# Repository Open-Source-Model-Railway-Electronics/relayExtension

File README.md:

# Relay Extension

These are general-purpose relay modules for use with DCC decoders like the [OS-Solenoid-Decoder](https://github.com/Open-Source-Model-Railway-Electronics/OS-Solenoid-Decoder).

## Variants

### SMD Version

### THT Version

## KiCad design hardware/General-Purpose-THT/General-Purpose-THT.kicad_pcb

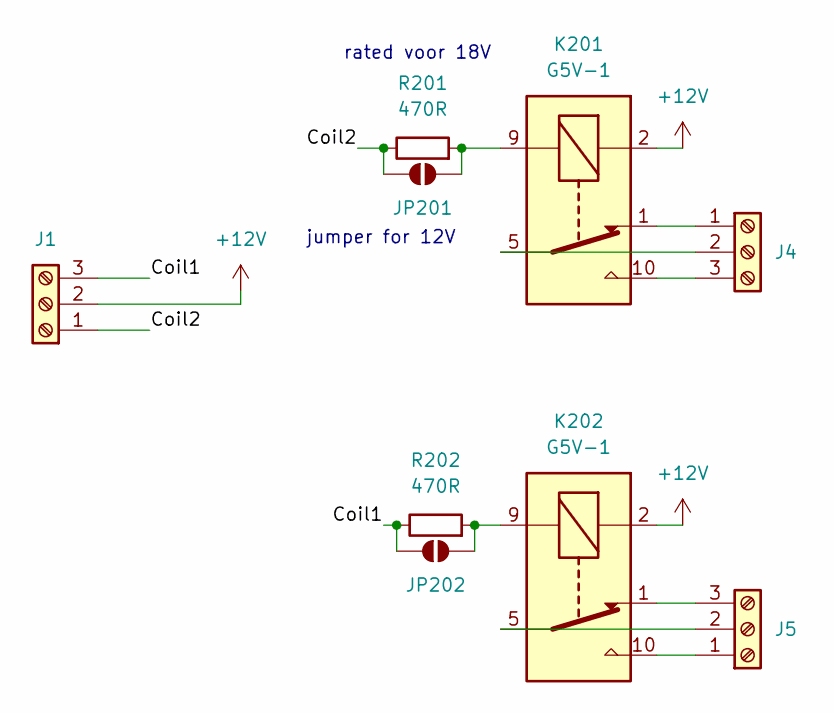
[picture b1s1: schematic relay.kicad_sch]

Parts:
J1: Screw_Terminal_01x03; connector_3.50mm_3P horizontal_MALE; JLCPCB Part# C6394074
J4: Screw_Terminal_01x03; PhoenixContact_MC_1,5_3-G-3.5_1x03_P3.50mm_Horizontal; JLCPCB Part# C22380440
J5: Screw_Terminal_01x03; PhoenixContact_MCV_1,5_3-G-3.5_1x03_P3.50mm_Vertical; Mating Part# C560231; JLCPCB Part# C192778
JP201, JP202: SolderJumper_2_Open; SolderJumper-2_P1.3mm_Open_RoundedPad1.0x1.5mm
K201, K202: G5V-1; Relay_SPDT_Omron_G5V-1
R201, R202: 470R; R_Axial_DIN0204_L3.6mm_D1.6mm_P7.62mm_Horizontal

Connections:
+12V: J1.2, K201.2, K202.2
/relay1/Coil1: J1.3, JP202.1 (A), R202.1
/relay1/Coil2: J1.1, JP201.1 (A), R201.1
unnamed: J4.1, K201.1
unnamed: J4.2, K201.5, K201.6
unnamed: J4.3, K201.10
unnamed: J5.1, K202.10
unnamed: J5.2, K202.5, K202.6
unnamed: J5.3, K202.1
unnamed: JP201.2 (B), K201.9, R201.2
unnamed: JP202.2 (B), K202.9, R202.2

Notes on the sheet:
jumper for 12V
rated voor 18V

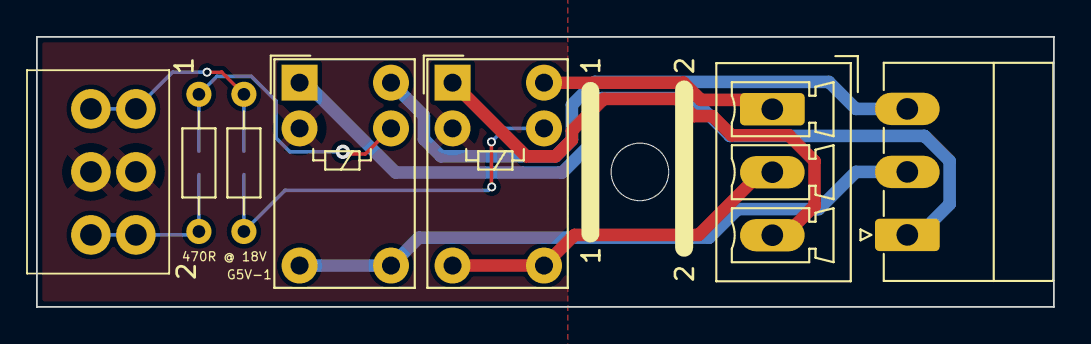
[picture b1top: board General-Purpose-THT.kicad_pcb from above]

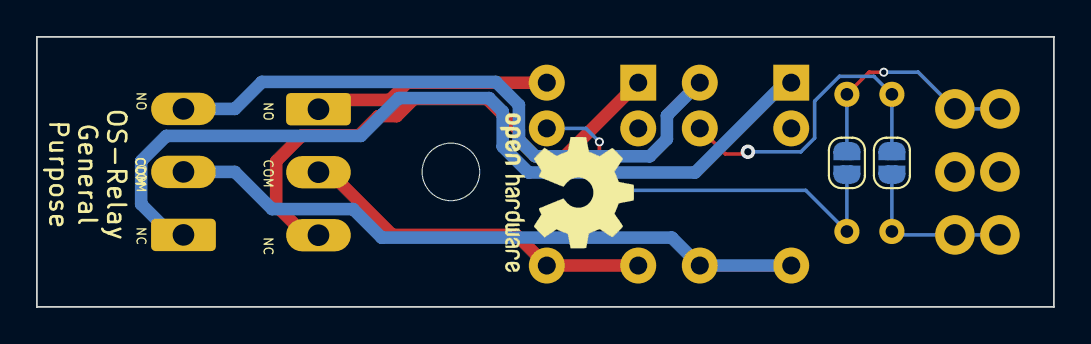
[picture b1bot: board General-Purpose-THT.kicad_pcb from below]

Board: 2 copper layers, 56.5 x 15.0 mm, 9 parts (2 on the bottom side), 11 nets.

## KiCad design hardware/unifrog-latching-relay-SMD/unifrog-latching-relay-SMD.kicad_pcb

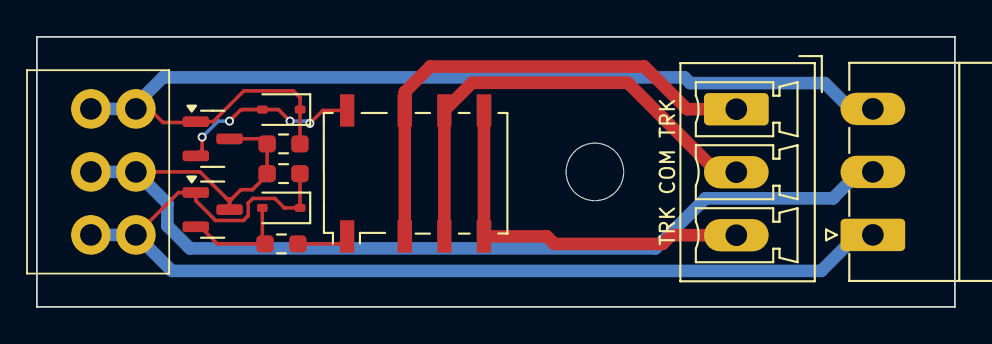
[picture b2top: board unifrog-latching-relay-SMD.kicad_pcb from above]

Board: 2 copper layers, 51.0 x 15.0 mm, 11 parts (0 on the bottom side), 9 nets.

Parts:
D3, D4: 1N4148WS; D_SOD-323
J1: Screw_Terminal_01x03; connector_3.50mm_3P horizontal_MALE
J4: Screw_Terminal_01x03; PhoenixContact_MC_1,5_3-G-3.5_1x03_P3.50mm_Horizontal
J6: Screw_Terminal_01x03; PhoenixContact_MCV_1,5_3-G-3.5_1x03_P3.50mm_Vertical
K2: G6KU-2; Relay_DPDT_Omron_G6K-2F-Y
Q3, Q4: NPN_TOR; SOT-23
R3, R4: 22k; R_0603_smalltext
R10: 680R; R_0603_smalltext

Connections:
/relay2/DCC_A: J6.1, K2.2, K2.7
/relay2/DCC_B: J6.3, K2.4, K2.5
/relay2/coilA: D4.1 (K), J1.1, J4.1, Q4.1 (B), R4.2
/relay2/coilB: D3.1 (K), J1.3, J4.3, Q3.1 (B), R3.2
/relay2/common: J1.2, J4.2, Q3.3 (C), Q4.3 (C), R3.1, R4.1
unnamed: D3.2 (A), K2.8, Q3.2 (E)
unnamed: D4.2 (A), Q4.2 (E), R10.1
unnamed: J6.2, K2.3, K2.6
unnamed: K2.1, R10.2

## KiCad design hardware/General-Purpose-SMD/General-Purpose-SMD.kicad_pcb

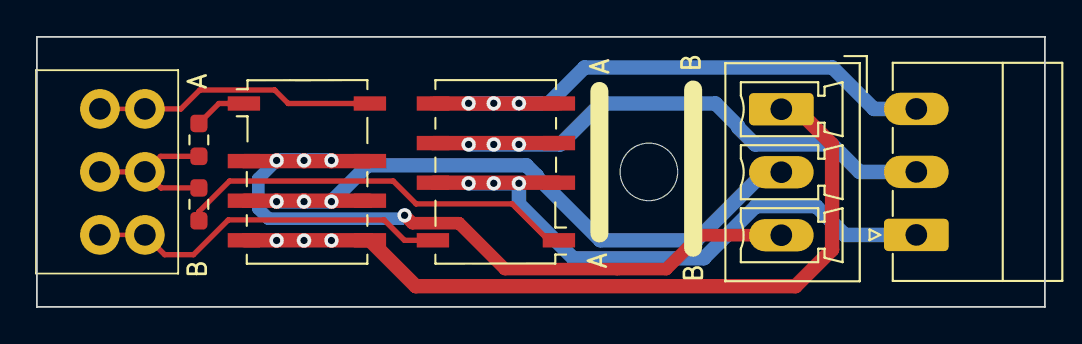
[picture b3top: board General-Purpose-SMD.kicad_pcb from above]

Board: 2 copper layers, 56.0 x 15.0 mm, 7 parts (0 on the bottom side), 11 nets.

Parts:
J1: Screw_Terminal_01x03; connector_3.50mm_3P horizontal_MALE
J4: Screw_Terminal_01x03; PhoenixContact_MC_1,5_3-G-3.5_1x03_P3.50mm_Horizontal
J5: Screw_Terminal_01x03; PhoenixContact_MCV_1,5_3-G-3.5_1x03_P3.50mm_Vertical
K1, K2: G6K-2F-Y-TR DC12; Relay_DPDT_Omron_G6K-2F-Y
R1, R2: 680R; R_0603_smalltext

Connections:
/relay1/COM1: J4.2, K1.3, K1.6
/relay1/COM2: J5.2, K2.3, K2.6
/relay1/Coil1: J1.3, K2.8
/relay1/Coil2: J1.1, K1.8
/relay1/NC1: J4.1, K1.2, K1.7
/relay1/NC2: J5.3, K2.2, K2.7
/relay1/NO1: J4.3, K1.4, K1.5
/relay1/NO2: J5.1, K2.4, K2.5
/relay1/V+: J1.2, R1.2, R2.2
unnamed: K1.1, R1.1
unnamed: K2.1, R2.1

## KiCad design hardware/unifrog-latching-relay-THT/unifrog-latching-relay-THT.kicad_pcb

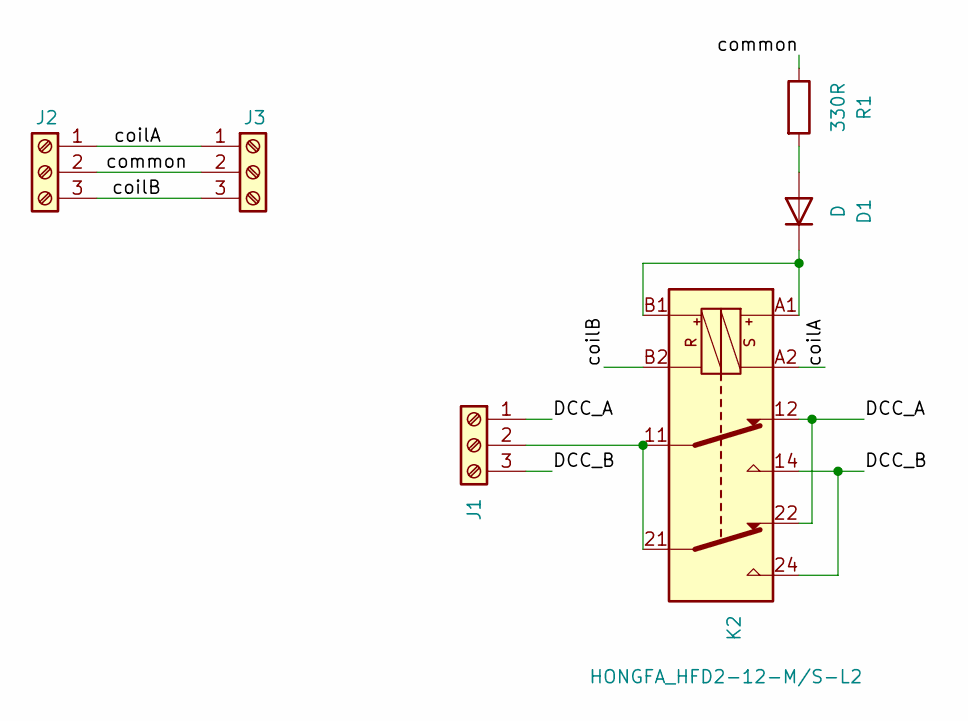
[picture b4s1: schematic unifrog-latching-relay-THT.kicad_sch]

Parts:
D1: D; D_DO-34_SOD68_P7.62mm_Horizontal
J1: Screw_Terminal_01x03; PhoenixContact_MCV_1,5_3-G-3.5_1x03_P3.50mm_Vertical; mating part# C560231; JLCPCB Part# C880555
J2: Screw_Terminal_01x03; connector_3.50mm_3P horizontal_MALE; JLCPCB Part# C6394074
J3: Screw_Terminal_01x03; PhoenixContact_MC_1,5_3-G-3.5_1x03_P3.50mm_Horizontal; Mating Part# C560213; JLCPCB Part# C880573
K2: HONGFA_HFD2-12-M/S-L2; Relay_DPDT_Omron_G6AK
R1: 330R; R_Axial_DIN0204_L3.6mm_D1.6mm_P7.62mm_Horizontal

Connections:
/DCC_A: J1.1, K2.12, K2.22
/DCC_B: J1.3, K2.14, K2.24
/coilA: J2.1, J3.1, K2.A2
/coilB: J2.3, J3.3, K2.B2
/common: J2.2, J3.2, R1.1
unnamed: D1.2 (A), R1.2
unnamed: D1.1 (K), K2.A1, K2.B1
unnamed: J1.2, K2.11, K2.21

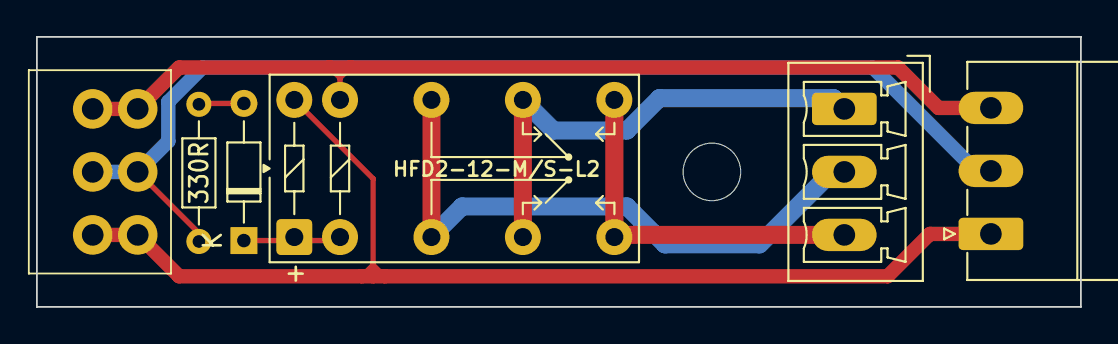
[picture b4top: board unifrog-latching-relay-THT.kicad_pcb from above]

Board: 2 copper layers, 58.0 x 15.0 mm, 6 parts (0 on the bottom side), 8 nets.

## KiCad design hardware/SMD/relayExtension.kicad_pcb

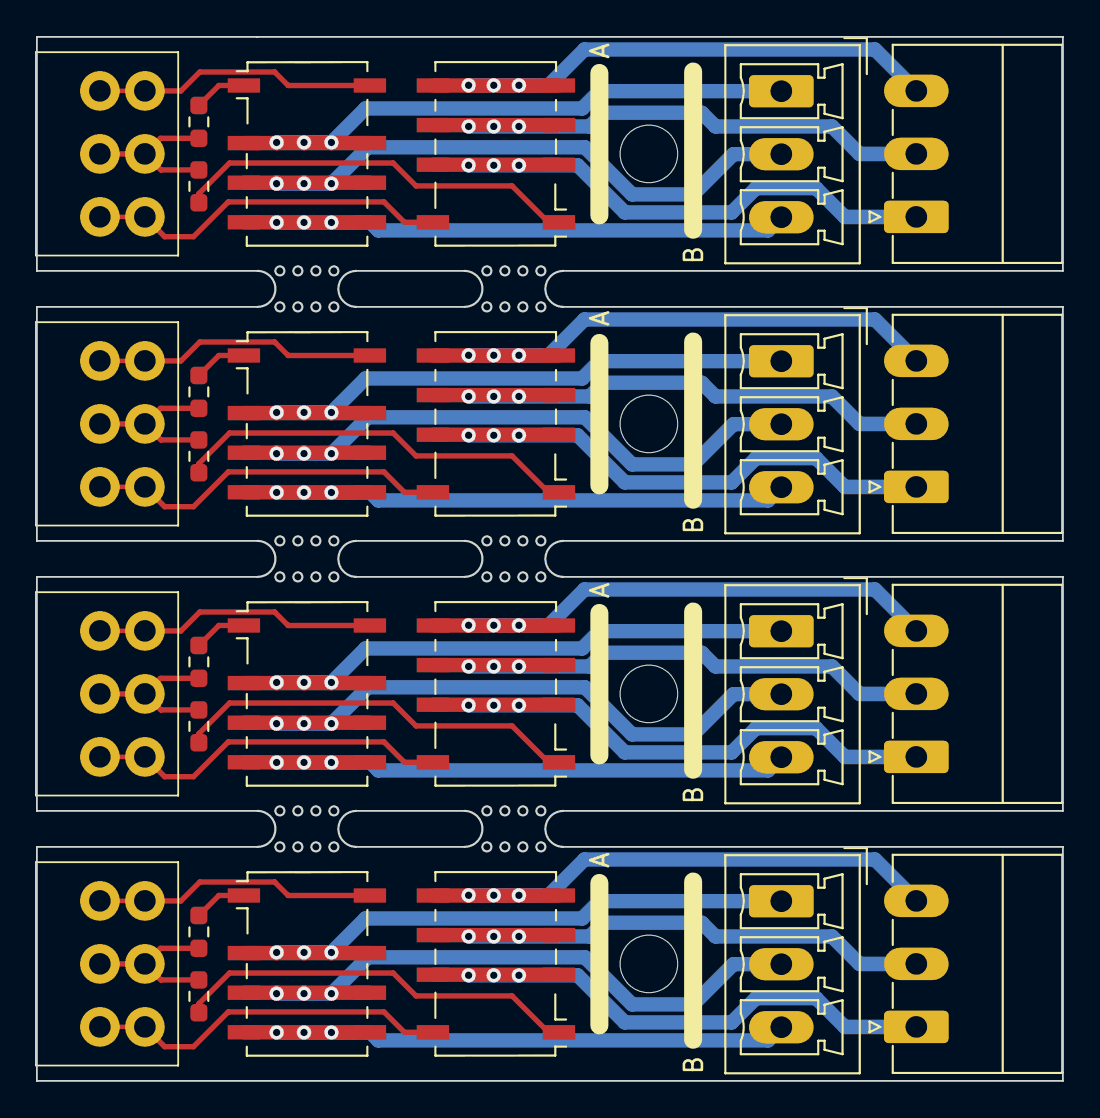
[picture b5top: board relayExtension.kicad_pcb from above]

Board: 2 copper layers, 57.0 x 58.0 mm, 28 parts (0 on the bottom side), 44 nets.

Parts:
J1, J2, J7, J10: Screw_Terminal_01x03; connector_3.50mm_3P horizontal_MALE
J3, J4, J8, J11: Screw_Terminal_01x03; PhoenixContact_MC_1,5_3-G-3.5_1x03_P3.50mm_Horizontal
J5, J6, J9, J12: Screw_Terminal_01x03; PhoenixContact_MCV_1,5_3-G-3.5_1x03_P3.50mm_Vertical
K1, K2, K3, K4, K5, K6, K7, K8: G6K-2F-Y-TR DC12; Relay_DPDT_Omron_G6K-2F-Y
R1, R2, R3, R4, R5, R6, R7, R8: 680R; R_0603_smalltext

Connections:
/relay1/COM1: J4.2, K1.3, K1.6
/relay1/COM2: J5.2, K2.3, K2.6
/relay1/Coil1: J1.3, K2.8
/relay1/Coil2: J1.1, K1.8
/relay1/NC1: J4.1, K1.2, K1.7
/relay1/NC2: J5.1, K2.2, K2.7
/relay1/NO1: J4.3, K1.4, K1.5
/relay1/NO2: J5.3, K2.4, K2.5
/relay1/V+: J1.2, R1.2, R2.2
/relay2/COM1: J3.2, K3.3, K3.6
/relay2/COM2: J6.2, K4.3, K4.6
/relay2/Coil1: J2.3, K4.8
/relay2/Coil2: J2.1, K3.8
/relay2/NC1: J3.1, K3.2, K3.7
/relay2/NC2: J6.1, K4.2, K4.7
/relay2/NO1: J3.3, K3.4, K3.5
/relay2/NO2: J6.3, K4.4, K4.5
/relay2/V+: J2.2, R3.2, R4.2
/relay3/COM1: J8.2, K5.3, K5.6
/relay3/COM2: J9.2, K6.3, K6.6
/relay3/Coil1: J7.3, K6.8
/relay3/Coil2: J7.1, K5.8
/relay3/NC1: J8.1, K5.2, K5.7
/relay3/NC2: J9.1, K6.2, K6.7
/relay3/NO1: J8.3, K5.4, K5.5
/relay3/NO2: J9.3, K6.4, K6.5
/relay3/V+: J7.2, R5.2, R6.2
/relay4/COM1: J11.2, K7.3, K7.6
/relay4/COM2: J12.2, K8.3, K8.6
/relay4/Coil1: J10.3, K8.8
/relay4/Coil2: J10.1, K7.8
/relay4/NC1: J11.1, K7.2, K7.7
/relay4/NC2: J12.1, K8.2, K8.7
/relay4/NO1: J11.3, K7.4, K7.5
/relay4/NO2: J12.3, K8.4, K8.5
/relay4/V+: J10.2, R7.2, R8.2
unnamed: K1.1, R1.1
unnamed: K2.1, R2.1
unnamed: K3.1, R3.1
unnamed: K4.1, R4.1
unnamed: K5.1, R5.1
unnamed: K6.1, R6.1
unnamed: K7.1, R7.1
unnamed: K8.1, R8.1

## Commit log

2025-06-17 added or renamed PNG preview
2025-06-17 added all files
2025-06-17 fixed 2 images
2025-06-19 Toegevoegd: handleiding (manual.odt)
2025-06-19 Hersteld: handleiding toegevoegd in docs/
2025-06-23 added data to readme.md
2025-10-27 added single variant for SMD relay to be made using V-cuts
2025-11-08 added files
2025-11-11 added manual placeholder
2025-11-13 redid the through-hole relay pcb
2025-11-13 finalized relays repo. Yet to do manual. Release is ready togo
2025-11-13 added all.png
2025-11-14 Made the manual for the OS-Relays
